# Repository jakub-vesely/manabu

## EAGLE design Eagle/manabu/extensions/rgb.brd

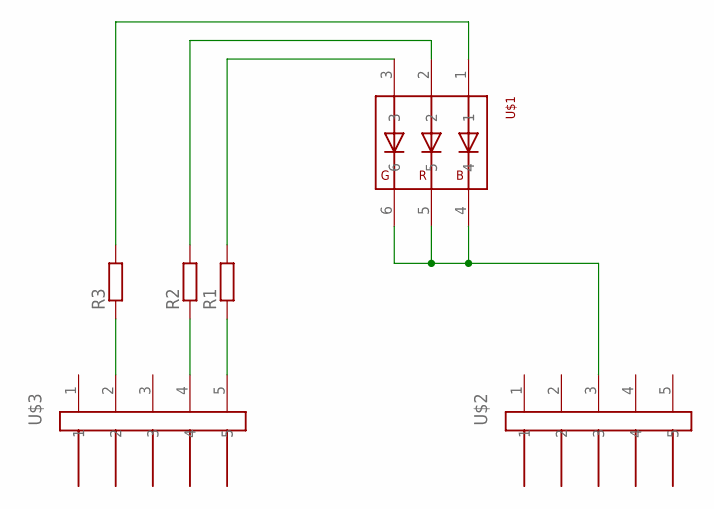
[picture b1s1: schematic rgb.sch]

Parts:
R1, R2, R3: R-EU_R0603; R0603
U$1: RGB_WW-FCE50TC-Q1
U$2, U$3: JUMPER5M

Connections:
GND: U$1.4, U$1.5, U$1.6, U$2.3
unnamed: R3.1, U$3.2
unnamed: R1.2, U$1.3
unnamed: R2.2, U$1.2
unnamed: R3.2, U$1.1
unnamed: R2.1, U$3.4
unnamed: R1.1, U$3.5

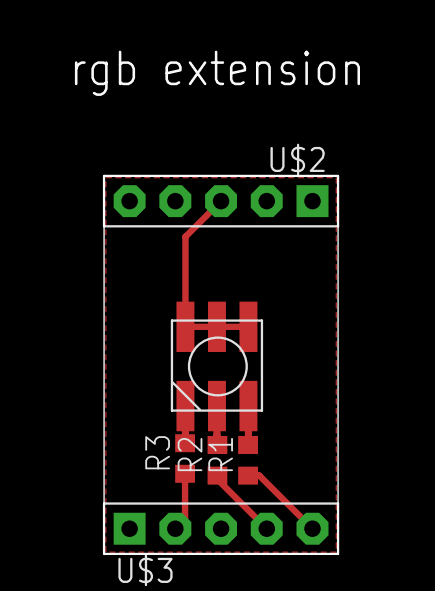
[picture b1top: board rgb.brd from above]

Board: 2 copper layers, 13.0 x 21.0 mm, 6 parts (0 on the bottom side), 7 nets.

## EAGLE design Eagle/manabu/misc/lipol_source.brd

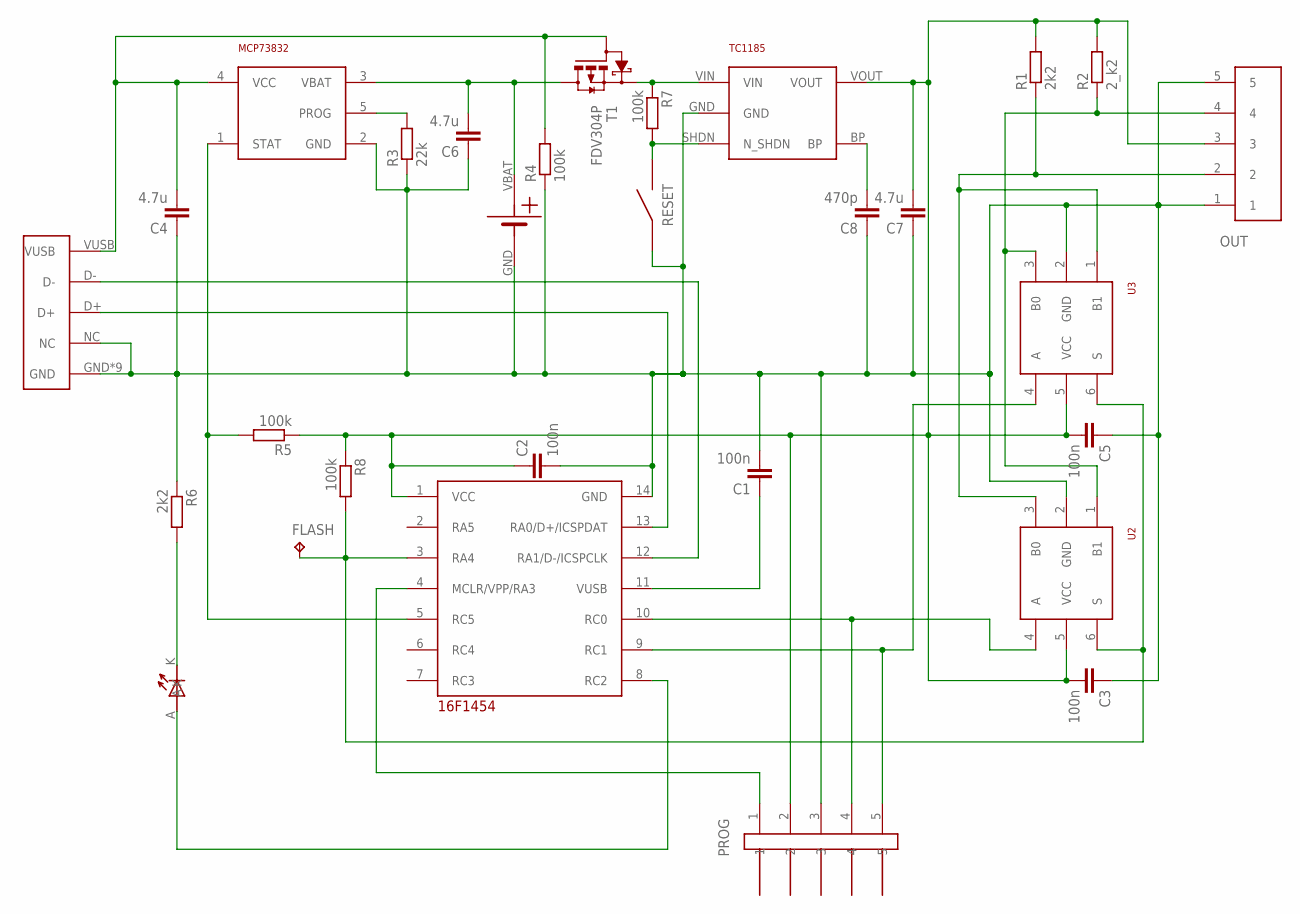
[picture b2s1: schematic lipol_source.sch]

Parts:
C1, C2, C3, C5: 100n; C0603K
C4, C6, C7: 4.7u; C0603K
C8: 470p; C0603K
D1: LED1.8
FLASH: TPTP10R; TP10R
MCP73832: MCP73831; SOT23-5
OUT: JUMPER5F-90
PROG: JUMPER5M
R1, R6: 2k2; R0603
R2: 2_k2; R0603
R3: 22k; R0603
R4, R5, R7, R8: 100k; R0603
RESET: BYTTON-B3U; BUTTON-B3U
T1: FDV304P; SOT23
TC1185: TC1185; SOT32-5
U1: 16F1454; TSSOP14
U2, U3: NC7SB3157P6X; SC70-6L
U$3: LIPOL_21X17
USB: USBMICRO; MICROUSB-MOLEX

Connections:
GND: C1.2, C2.2, C3.1, C4.1, C5.1, C6.1, C7.1, C8.1, MCP73832.2 (GND), OUT.1, OUT.5, PROG.3, R3.1, R4.1, R6.1, RESET.P$1, TC1185.GND, U1.14 (GND), U2.2 (GND), U3.2 (GND), U$3.GND, USB.GND, USB.GND1 (GND), USB.GND2 (GND), USB.GND3 (GND), USB.GND4 (GND), USB.NC, USB.P$1 (GND), USB.P$2 (GND), USB.P$3 (GND), USB.P$6 (GND)
unnamed: FLASH.TP, R8.2, U1.3 (RA4), U2.6 (S), U3.6 (S)
unnamed: U1.12 (RA1/D-/ICSPCLK), USB.D-
unnamed: C1.1, U1.11 (VUSB)
unnamed: PROG.4, U1.10 (RC0), U2.4 (A)
unnamed: U1.13 (RA0/D+/ICSPDAT), USB.D+
unnamed: OUT.2, R1.1, U2.3 (B0), U3.1 (B1)
unnamed: PROG.5, U1.9 (RC1), U3.4 (A)
unnamed: C6.2, MCP73832.3 (VBAT), T1.D, U$3.VBAT
unnamed: C4.2, MCP73832.4 (VCC), R4.2, T1.G, USB.VUSB
unnamed: OUT.4, R2.1, U2.1 (B1), U3.3 (B0)
unnamed: MCP73832.5 (PROG), R3.2
unnamed: R7.1, T1.S, TC1185.VIN
unnamed: MCP73832.1 (STAT), R5.2, U1.5 (RC5)
unnamed: PROG.1, U1.4 (MCLR/VPP/RA3)
unnamed: D1.K, R6.2
unnamed: D1.A, U1.8 (RC2)
unnamed: C8.2, TC1185.BP
unnamed: R7.2, RESET.P$2, TC1185.SHDN (N_SHDN)
VCC: C2.1, C3.2, C5.2, C7.2, OUT.3, PROG.2, R1.2, R2.2, R5.1, R8.1, TC1185.VOUT, U1.1 (VCC), U2.5 (VCC), U3.5 (VCC)

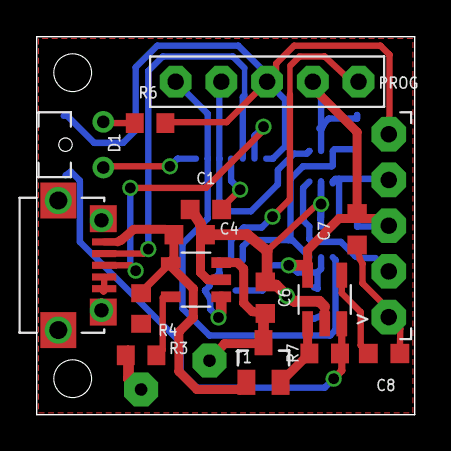
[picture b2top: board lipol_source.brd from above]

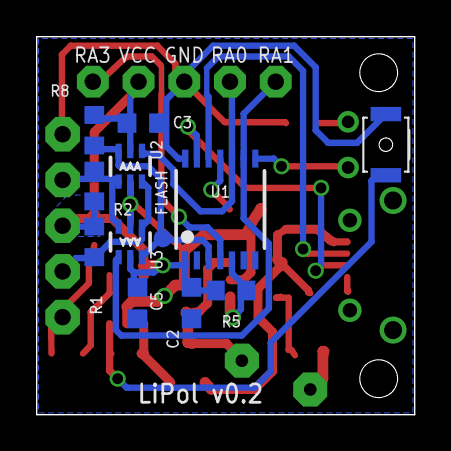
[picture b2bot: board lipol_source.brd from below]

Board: 2 copper layers, 21.0 x 21.0 mm, 29 parts (12 on the bottom side), 20 nets.

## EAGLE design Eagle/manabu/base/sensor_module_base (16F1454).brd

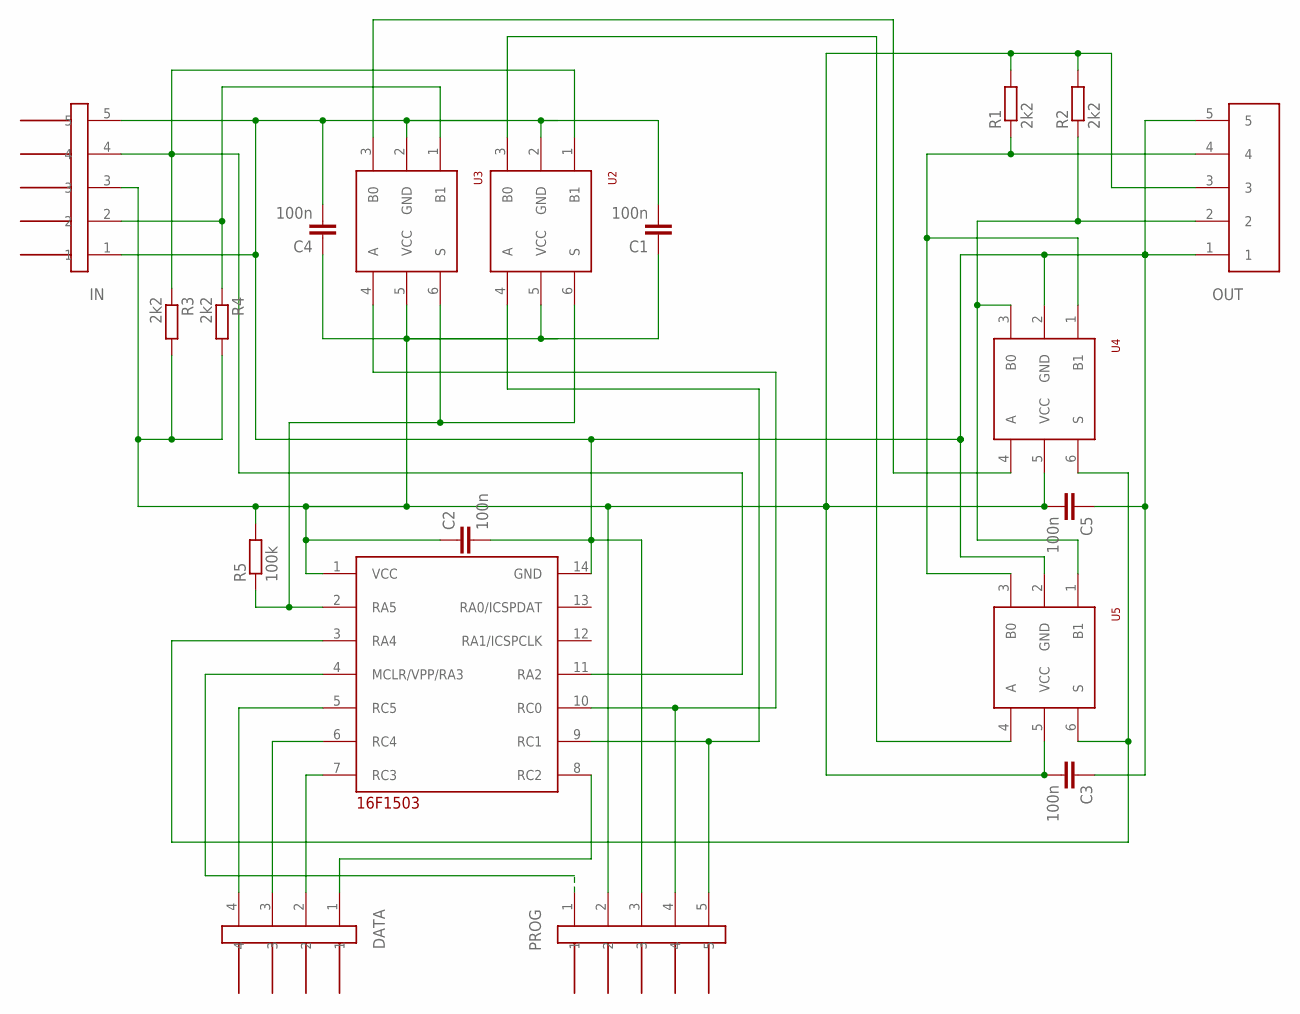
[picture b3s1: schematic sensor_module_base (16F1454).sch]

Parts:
C1, C2, C3, C4, C5: 100n; C0603K
DATA: JUMPER4M
IN: JUMPER5M-90
OUT: JUMPER5F-90
PROG: JUMPER5M
R1, R2, R3, R4: 2k2; R0603
R5: 100k; R0603
U1: 16F1454; TSSOP14
U2, U3, U4, U5: NC7SB3157P6X; SC70-6L

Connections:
GND: C1.2, C2.2, C3.1, C4.2, C5.1, IN.1, IN.5, OUT.1, OUT.5, PROG.3, U1.14 (GND), U2.2 (GND), U3.2 (GND), U4.2 (GND), U5.2 (GND)
unnamed: U1.3 (RA4), U4.6 (S), U5.6 (S)
unnamed: PROG.5, U1.9 (RC1), U2.4 (A)
unnamed: DATA.2, U1.7 (RC3)
unnamed: PROG.4, U1.10 (RC0), U3.4 (A)
unnamed: OUT.4, R1.1, U4.1 (B1), U5.3 (B0)
unnamed: U3.3 (B0), U4.4 (A)
unnamed: IN.2, R4.1, U3.1 (B1)
unnamed: R5.1, U1.2 (RA5), U2.6 (S), U3.6 (S)
unnamed: OUT.2, R2.1, U4.3 (B0), U5.1 (B1)
unnamed: IN.4, R3.1, U1.11 (RA2), U2.1 (B1)
unnamed: DATA.4, U1.5 (RC5)
unnamed: PROG.1, U1.4 (MCLR/VPP/RA3)
unnamed: DATA.3, U1.6 (RC4)
unnamed: DATA.1, U1.8 (RC2)
unnamed: U2.3 (B0), U5.4 (A)
VCC: C1.1, C2.1, C3.2, C4.1, C5.2, IN.3, OUT.3, PROG.2, R1.2, R2.2, R3.2, R4.2, R5.2, U1.1 (VCC), U2.5 (VCC), U3.5 (VCC), U4.5 (VCC), U5.5 (VCC)

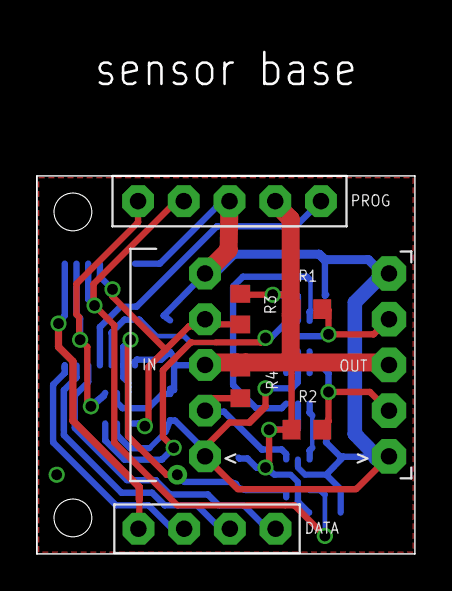
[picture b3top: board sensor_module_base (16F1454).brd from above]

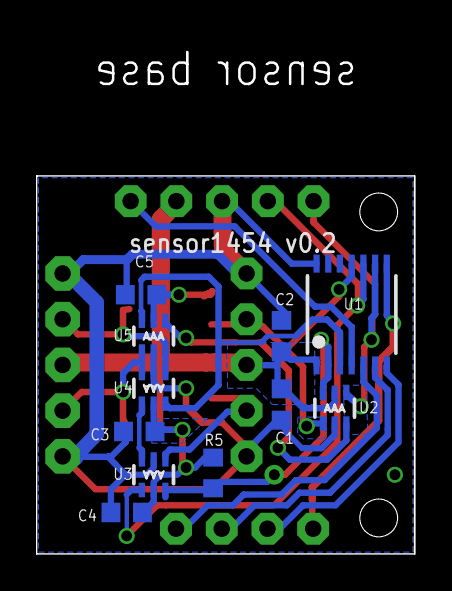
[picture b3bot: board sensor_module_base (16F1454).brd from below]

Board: 2 copper layers, 21.0 x 21.0 mm, 19 parts (11 on the bottom side), 17 nets.

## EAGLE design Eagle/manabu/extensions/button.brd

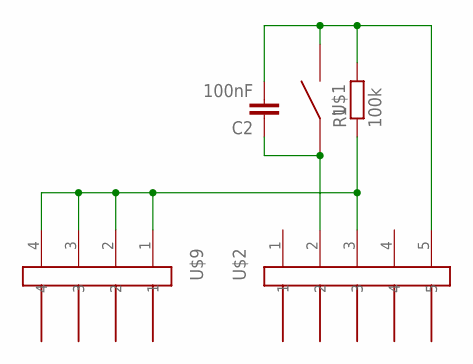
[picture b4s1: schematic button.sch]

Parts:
C2: 100nF; C0603K
R1: 100k; R0603
U$1: BUTTON_7X7
U$2: JUMPER5M
U$9: JUMPER4M

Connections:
AA: C2.2, R1.2, U$1.B1, U$1.B2, U$2.5
GND: R1.1, U$2.3, U$9.1, U$9.2, U$9.3, U$9.4
VCC: C2.1, U$1.A1, U$1.A2, U$2.2

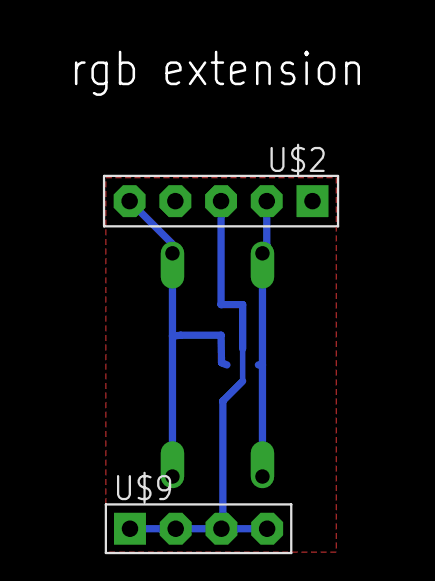
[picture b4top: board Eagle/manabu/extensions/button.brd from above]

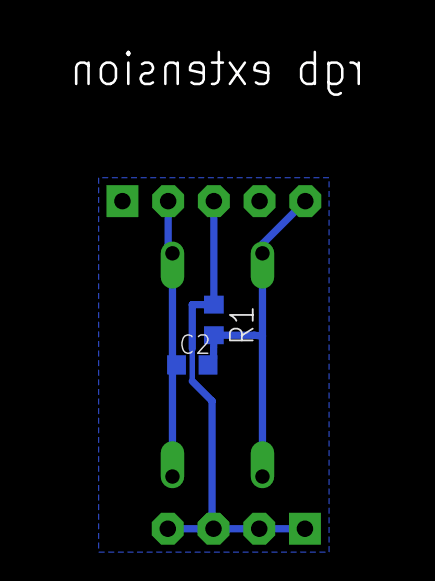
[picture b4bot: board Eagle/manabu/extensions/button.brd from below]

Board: 2 copper layers, 5 parts (2 on the bottom side), 3 nets.

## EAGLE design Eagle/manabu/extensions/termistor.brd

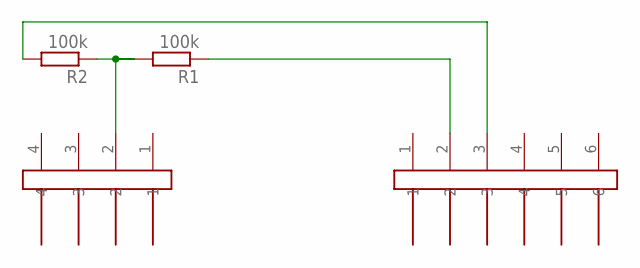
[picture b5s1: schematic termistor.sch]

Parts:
R1, R2: 100k; R0603
U$8: JUMPER6M
U$9: JUMPER4M

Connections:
unnamed: R1.2, R2.1, U$9.2
unnamed: R1.1, U$8.2
unnamed: R2.2, U$8.3

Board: 2 copper layers, 4 parts (0 on the bottom side), 3 nets, no tracks yet.

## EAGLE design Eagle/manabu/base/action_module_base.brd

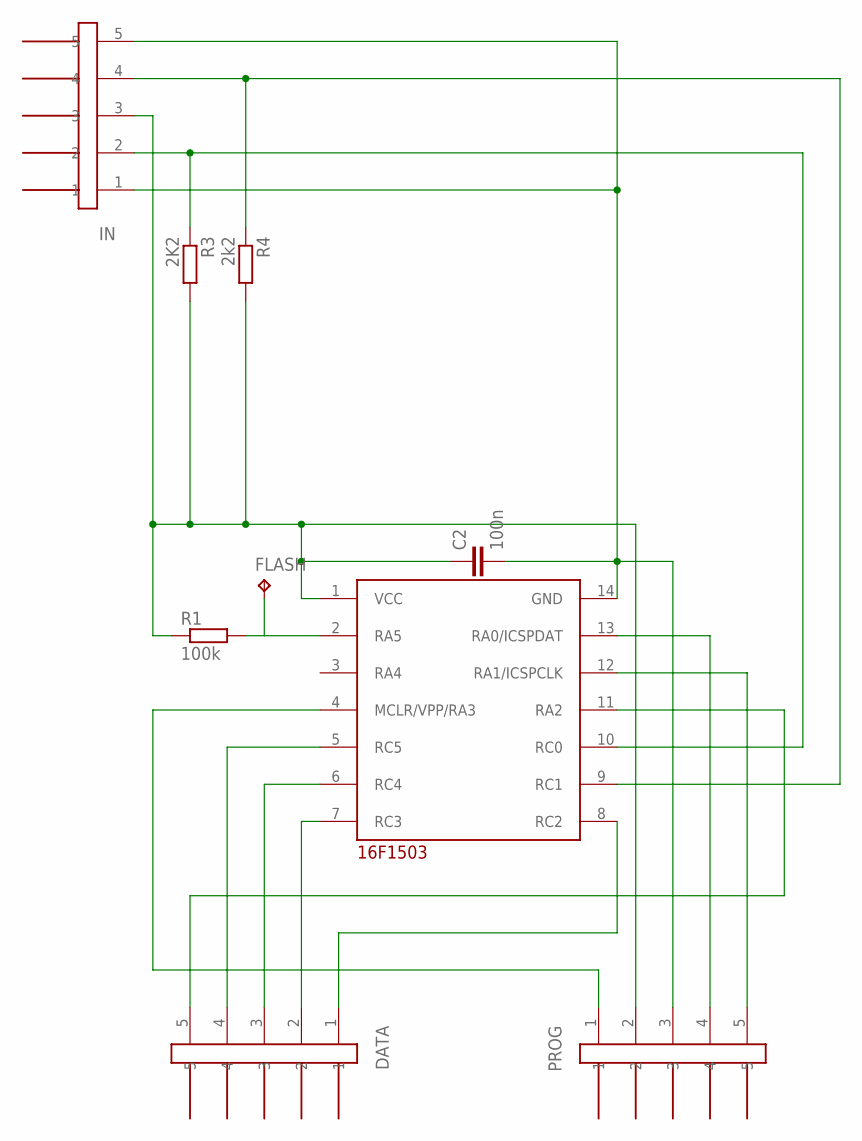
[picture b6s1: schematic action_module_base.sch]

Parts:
C2: 100n; C0603K
DATA: JUMPER5M
FLASH: TPTP10R; TP10R
IN: JUMPER5M-90
PROG: JUMPER5M
R1: 100k; R0603
R3: 2K2; R0603
R4: 2k2; R0603
U1: 16F103; TSSOP14

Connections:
GND: C2.2, IN.1, IN.5, PROG.3, U1.14 (GND)
unnamed: DATA.2, U1.7 (RC3)
unnamed: IN.2, R3.1, U1.10 (RC0)
unnamed: FLASH.TP, R1.2, U1.2 (RA5)
unnamed: IN.4, R4.1, U1.9 (RC1)
unnamed: DATA.5, U1.11 (RA2)
unnamed: DATA.4, U1.5 (RC5)
unnamed: PROG.1, U1.4 (MCLR/VPP/RA3)
unnamed: PROG.4, U1.13 (RA0/ICSPDAT)
unnamed: PROG.5, U1.12 (RA1/ICSPCLK)
unnamed: DATA.3, U1.6 (RC4)
unnamed: DATA.1, U1.8 (RC2)
VCC: C2.1, IN.3, PROG.2, R1.1, R3.2, R4.2, U1.1 (VCC)

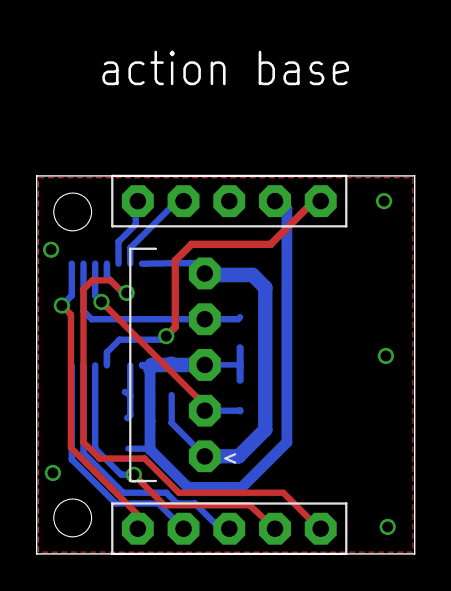
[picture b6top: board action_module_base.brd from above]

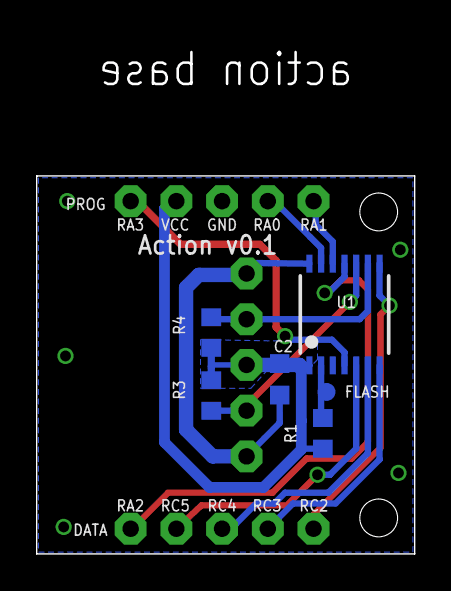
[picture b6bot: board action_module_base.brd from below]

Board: 2 copper layers, 21.0 x 21.0 mm, 9 parts (6 on the bottom side), 13 nets.

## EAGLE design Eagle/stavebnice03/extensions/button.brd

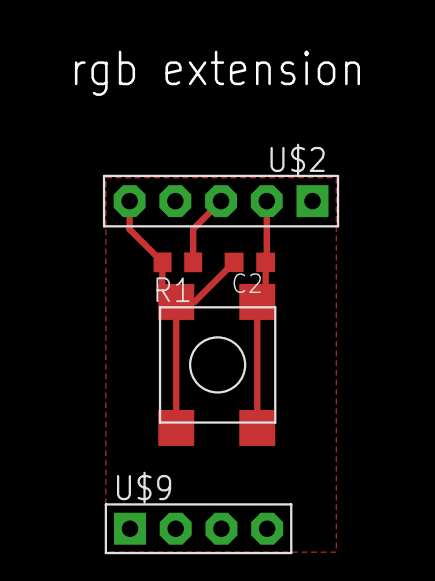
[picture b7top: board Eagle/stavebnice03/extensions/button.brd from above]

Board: 2 copper layers, 5 parts (0 on the bottom side), 3 nets.

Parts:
C2: 100nF; C0603K
R1: 100k; R0603
U$1: BUTTON_6.3X6.3; BUTTON_6.2X6.2
U$2: JUMPER5M
U$9: JUMPER4M

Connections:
AA: C2.2, R1.2, U$1.P$2, U$1.P$4, U$2.5
GND: R1.1, U$2.3, U$9.1, U$9.2, U$9.3, U$9.4
VCC: C2.1, U$1.P$1, U$1.P$3, U$2.2

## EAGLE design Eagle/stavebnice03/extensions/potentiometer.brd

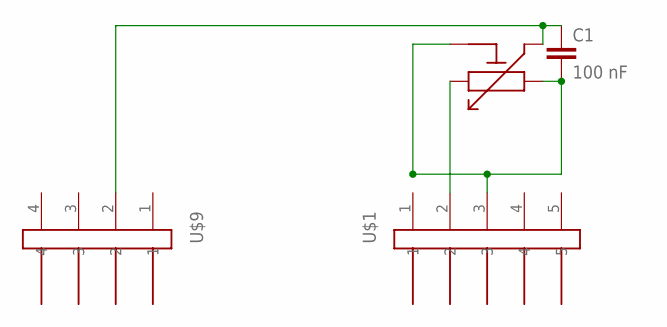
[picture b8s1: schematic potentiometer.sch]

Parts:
C1: 100 nF; C0805
U$1: JUMPER5M
U$2: POTENTIOMETER-RK09
U$9: JUMPER4M

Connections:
GND: C1.2, U$1.3, U$2.1, U$2.GND1 (GND), U$2.GND2 (GND)
unnamed: C1.1, U$2.2, U$9.2
unnamed: U$1.2, U$2.3

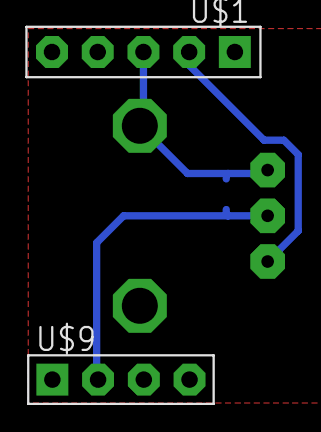
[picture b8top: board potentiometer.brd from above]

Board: 2 copper layers, 4 parts (1 on the bottom side), 3 nets.

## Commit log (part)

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2015-01-11 created folder stavebnice03 and created RGB module (I2C not tested yet)
2015-01-11 data are transferred by I2C from interface to RGB
2015-01-16 simple control application + storing data to internal eeprom in interface module
2015-01-22 transfer form mplab to mplab x. Resp. from htc compiler to xc compiler + added support for high endurance flash
2015-01-23 fix of bug:body can't be i header + support for commands
2015-01-25 RGB mode changeing by an application
2015-01-27 try to fix a bug. broadcast data are not received when a read is done but I was not successful, a workaround applied.
2015-01-27 I moved last workaround to a device layer to application doesn't have to solve a hardware issue.
2015-02-28 library with used components
2015-03-04 refactoring: last functionality without boroadcast I2C messages
2015-03-04 box design ideas
2015-03-06 remove an user file
2015-03-06 refactoring - functionality doesn't change
2015-03-06 functionality for potentiometer and butom, now I'm albe to control descendent without desktop application
2015-03-07 module is able to switch between input and output and resend a state when is changed
2015-03-08 read from i2c
2015-03-08 repeated write
2015-03-14 coommon functionalit separated from rgb specific functionalit
2015-03-17 base board design
2015-03-24 bootloader base
2015-03-24 hex file processing
2015-03-24 i2c message proceesing moved from interupt to the main loop
2015-03-26 input connector moved closer to an edge, changed pads to octogonal, moved IO connectors (a little bit)
2015-03-26 1th print version of 5 pin interface module
2015-03-29 modul on an output may be rotated or disconnected and and connected again and a communication should continue.
2015-03-29 project for testing input and output connectivity on a just builded module.
2015-03-29 potentiometer board
2015-03-29 board ready for a print
2015-03-29 potentiometer shell
2015-04-01 fixed a HE memory position on 16F1503
2015-04-01 not done yet
2015-04-04 main file name changed
2015-04-04 hex file changing
2015-04-04 test program for a bootloader
2015-04-06 ifdefs added
    test program is stored and run
2015-04-06 ignore buid folders
2015-04-06 code is loaded through the i2c and then is run + line ending
2015-04-07 main program start on 0x100 solved checksum version and program interupt redirection
2015-04-07 when bootloader is loaded rest of memor is filled 0x1 which is instruction for reset after pressing the button program is loaded read should not freeze the program now
2015-04-08 minor changes
2015-04-08 AAA source board
2015-04-08 action module board
2015-04-09 it is a little bit more memory efective
2015-04-09 changed data format in text editor + now is posible to copy paste + last directory is partialy persistant mow
2015-04-09 gitignoe extended
2015-04-09 i2c handling added to botttest program
2015-04-10 bottloader memory part preservation
2015-04-11 bootlader write a program, it is run and change flag byte according a direction in next run is rum a program without writing them again
2015-04-11 it should protect bootloader againts rewriting
2015-04-11 bootloader program - not finished yew
2015-04-11 a new cdc_serial_emulator is base of a new Interface the old one have some toubles with arrays and I never find where the problem is
2015-04-12 bootloader finished !!!
2015-04-12 program starts on 0x100
2015-04-12 bootloader to common i2c file, not finished
2015-04-14 common Flash code is used now
2015-04-14 code should be more robust now I2C responze is sent before flash write is called
2015-04-14 booting adjustment It looks more stable now but sometimes data doesnt retutn as previous cases
2015-04-16 was added check for boot loader polcy
2015-04-16 added QCustomPlot library
2015-04-16 there was a lot of error in first run after booting
2015-04-16 added status windiow + FID_COMMAND_FLASH_LOAD_CHECK renamed to FID_COMMAND_FLASH_SET_BOOT_FLAG
2015-04-27 added baterry cell to library
2015-04-27 I did an order in Eagle files
2015-04-27 QCustomPlot test
2015-05-01 1/3AAA goes though added stabiliser PMOSFET and USB
2015-05-01 not finished board
2015-05-06 interface project has been replaced by a new project derived form a microchip low pin count development kit code. Interface_new which was from these project too doesnt work for pic 16F4554. I know wh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
2015-05-07 combining i2c for pic18 and pic16. doesnt work for pic 16 properly yet
2015-05-07 fix paths for bootloader
2015-05-07 oscilator frequency, i'm not realy sure by this commit...
2015-05-09 all projects are builuble again (paths) + all projects have the same structure (project as main directory)
2015-05-09 documentation to used processors
2015-05-10 minor changes in rgb project
2015-05-10 fix of bug. potentiometere initialization was in a wrong function
2015-05-10 dioda is lithing when message was not deliveried to output module
2015-05-10 project versions for bootloader and without
2015-05-10 problem with i2c in reverse output mode. not solved
2015-05-11 file structure for io test
2015-05-19 added wire from input bus to an iterrupt pin
2015-05-19 dist should not be pressent i a repository
2015-05-19 fixed programmer
2015-05-19 none bash should be in a repository
2015-05-19 potentiometter configuration renamed
2015-05-19 potentiometter improvenmet - initialization should not be done in each state request
2015-05-23 module communication without lags - doesnt work yet
2015-05-24 tree modules communication it works but I have to send a second module state all the time
2015-05-25 three modules communication without artefacts. finally!!!
2015-05-30 li-pol source
2015-05-30 Module type command
2015-05-30 It looks it is more reliable with a wait between a flash write and a reset
2015-05-30 no .bash shoul be present in repositor
2015-05-30 bootloader should fill unused memory to now there is no program present when is loaded to already filled chip
2015-05-30 Plot window onl when any program is already loaded to a chip
2015-05-30 rgb project support a bootloader
2015-05-31 arthmetic-logic module suport bootlader and works as invertor
2015-05-31 interface works with common main.c file and supports set state again
2015-06-04 base and battery module size increeased to 22x22
2015-06-05 LED resistor increased to a size 0805
2015-06-05 module type
2015-06-10 adjutet elemet values
2015-06-19 added pin and resistor to stay in bootloader + changed size back to 21x21 mm
2015-06-19 rgb extension module + ignore eagle working files
2015-06-19 changed supply to 3.25 V because of LF PIC
2015-06-19 I using system settings for PWM now
2015-06-19 it hould not be present in a repository because is working file
2015-06-21 minor element position changes
2015-06-21 removed COMMONOANODE option, it doesnt work well + added RGB calibration
2015-06-21 removed ROM option because it is alread set by anther wa
2015-06-25 termistor, buton a two-buttons extension
2015-06-25 i forgot to refactot fuctionId in program too
2015-06-25 added ProcessCommandModuleTypeSpecific() function + changed calibration for a new RGB led
2015-06-25 fix of bugs on rgb and lipol board + a few minor changes
2015-06-25 added JUMPER2M + some minor changes on lipol batery
2015-06-26 added counter for refreshing output
2015-06-26 PORT replaced by LAT for switchers.
2015-06-26 refactoring TRIS and LAT moved to one #ifdef
2015-06-26 state is MAX by default for the interface module
2015-06-26 I dont understant this behavior well but I dont have tim to look for it now. I added there FIXME, and hopefully fix it later
2015-06-26 voltage suply decreased for potenciometer module too
2015-06-26 g_state splited to inState and outState (potentiometer is able to combine it)
2015-06-29 setting of TRIS is not necesser when I dont use PORT
2015-06-29 resolved sending no data to output when input is expected, mainl in the case of flashing
2015-06-30 C0603 changed to C0603K with wider space between soldering areas
2015-07-01 state work in 10 bit mode now. PWM on RGB still use 8 bit value (it is recalculated)
2015-07-01 charge indication moved to the begin of a ProcessModuleFunctionality() it must be processed undependently to an usb state
2015-07-02 solved state when hardware doesn't response it still not solved hardware reconnection
2015-07-03 getting and setting of a mode from program to the RGB module
2015-07-03 Low pin count development kit support removed. it is not necassar an more and also it is not voltage compatible now
2015-07-04 interface should have mode persistant too
2015-07-09 shells for 3d print
2015-07-18 power save mode for interface, not finished
2015-07-18 power save mode for the interface module - 0.7mA, it could be better
2015-07-19 removed PIC18F14K50 support in i2c file
2015-07-20 minor changes in a lipol board
2015-07-20 power save - 110 uA after reset resp. 70 uA after usb disconnection
2015-07-20 fix of bug. there missed INVERT_OUTPUT_TRIS = false; in some i2c methords.
    there is still oneopen issue with a sleep mode dosnt work connected potentiometer and led. it works without it
2015-07-20 debbug message "Readed data are uncomplete." has been extended
2015-07-23 uncommented forgotten charging led routine
2015-07-23 layer coloring and place drawing moved to docu layer + changed sizes of names and values
2015-07-24 interface provides max state to output by default again
2015-07-24 RGB start with zero in state, it should not light when doesn't know how much
2015-07-27 bootloader for the interface module - not finished
2015-07-30 removed unused project
2015-07-30 adjusted program space for interface + removed unused file
2015-07-30 quick hack. program for the interface module is larger. Interface programming is not finihed yet
2015-07-30 interface specific code for bootloader
2015-08-01 interface flashing finished !!!
2015-08-01 added bootloder touch point and pull up resistor to switcher + increased interface led resistor, it lighted too much
2015-08-23 refactoring and program adjustment
    now id interface and layer1 module in one window. bootloader is modal dialog and debug messages are writen to a log window
2015-08-28 changes for pcb making by a seed studio
2015-08-29 USB Device description changed
2015-08-29 porojects renamed to manabu and moved to the same directory
2015-08-30 user should not be in a repositor
2015-08-30 rgb is in 10bit mode now + potentiometer calibration
2015-08-30 Interface to bootloader menu name changed
2015-09-04 changes for running on linux
2015-09-07 application try to connect to a device when is connected but closed. (because of linux)
2015-09-07 adjusted current shells and added generic sensor and action shells
2015-09-08 fix of bug, sometimes in lookad luike modulle was disconnected just before was opened on linux
2015-09-08 red to red mode is now without white and black
2015-09-08 program space save (the same behavior)
2015-09-18 added module project Generator - it doesn't work yet
2015-09-18 just a few optimalization on the sensor board
2015-09-18 added sensor like bord with chil 16F1454 (bor bluetooth, wifi,...)
2015-09-18 io test is more optimal now. also there was replaced LAT instead of PORT. there is a stange bug when I reset two port bits one by one the first is not reset. (may be just on linux cross compiller) + 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
2015-09-18 just changed languageToolchainVersion
2015-09-18 changed procesor type for potentiometer
2015-09-18 PORT replaced by LAT. When is reset two port bits one by other the first is not reseted. probably a linux(?) compiler error/
2015-09-23 timer for plot decreased to 500 ms
2015-09-23 added button 12x12 and then used in button extension
2015-09-23 enlarge delay in the IO_test
2015-09-23 changed a processor type for the A-L module
2015-10-27 invert output functionality moved to lipol module port A4 to be as same as on other modules (bootloader reset pin will have to be changed for lipol module)
2016-04-09 GetModeCount to all projects
2016-04-09 Temperature mode for the RGB module
2016-04-09 invert light temperature to have yellow when is RGB connected directly to source module.
2016-04-09 set logic module as inverter
2016-04-09 I forgot the github repository is just part of local repository so merged files has to be moved to correct directories
